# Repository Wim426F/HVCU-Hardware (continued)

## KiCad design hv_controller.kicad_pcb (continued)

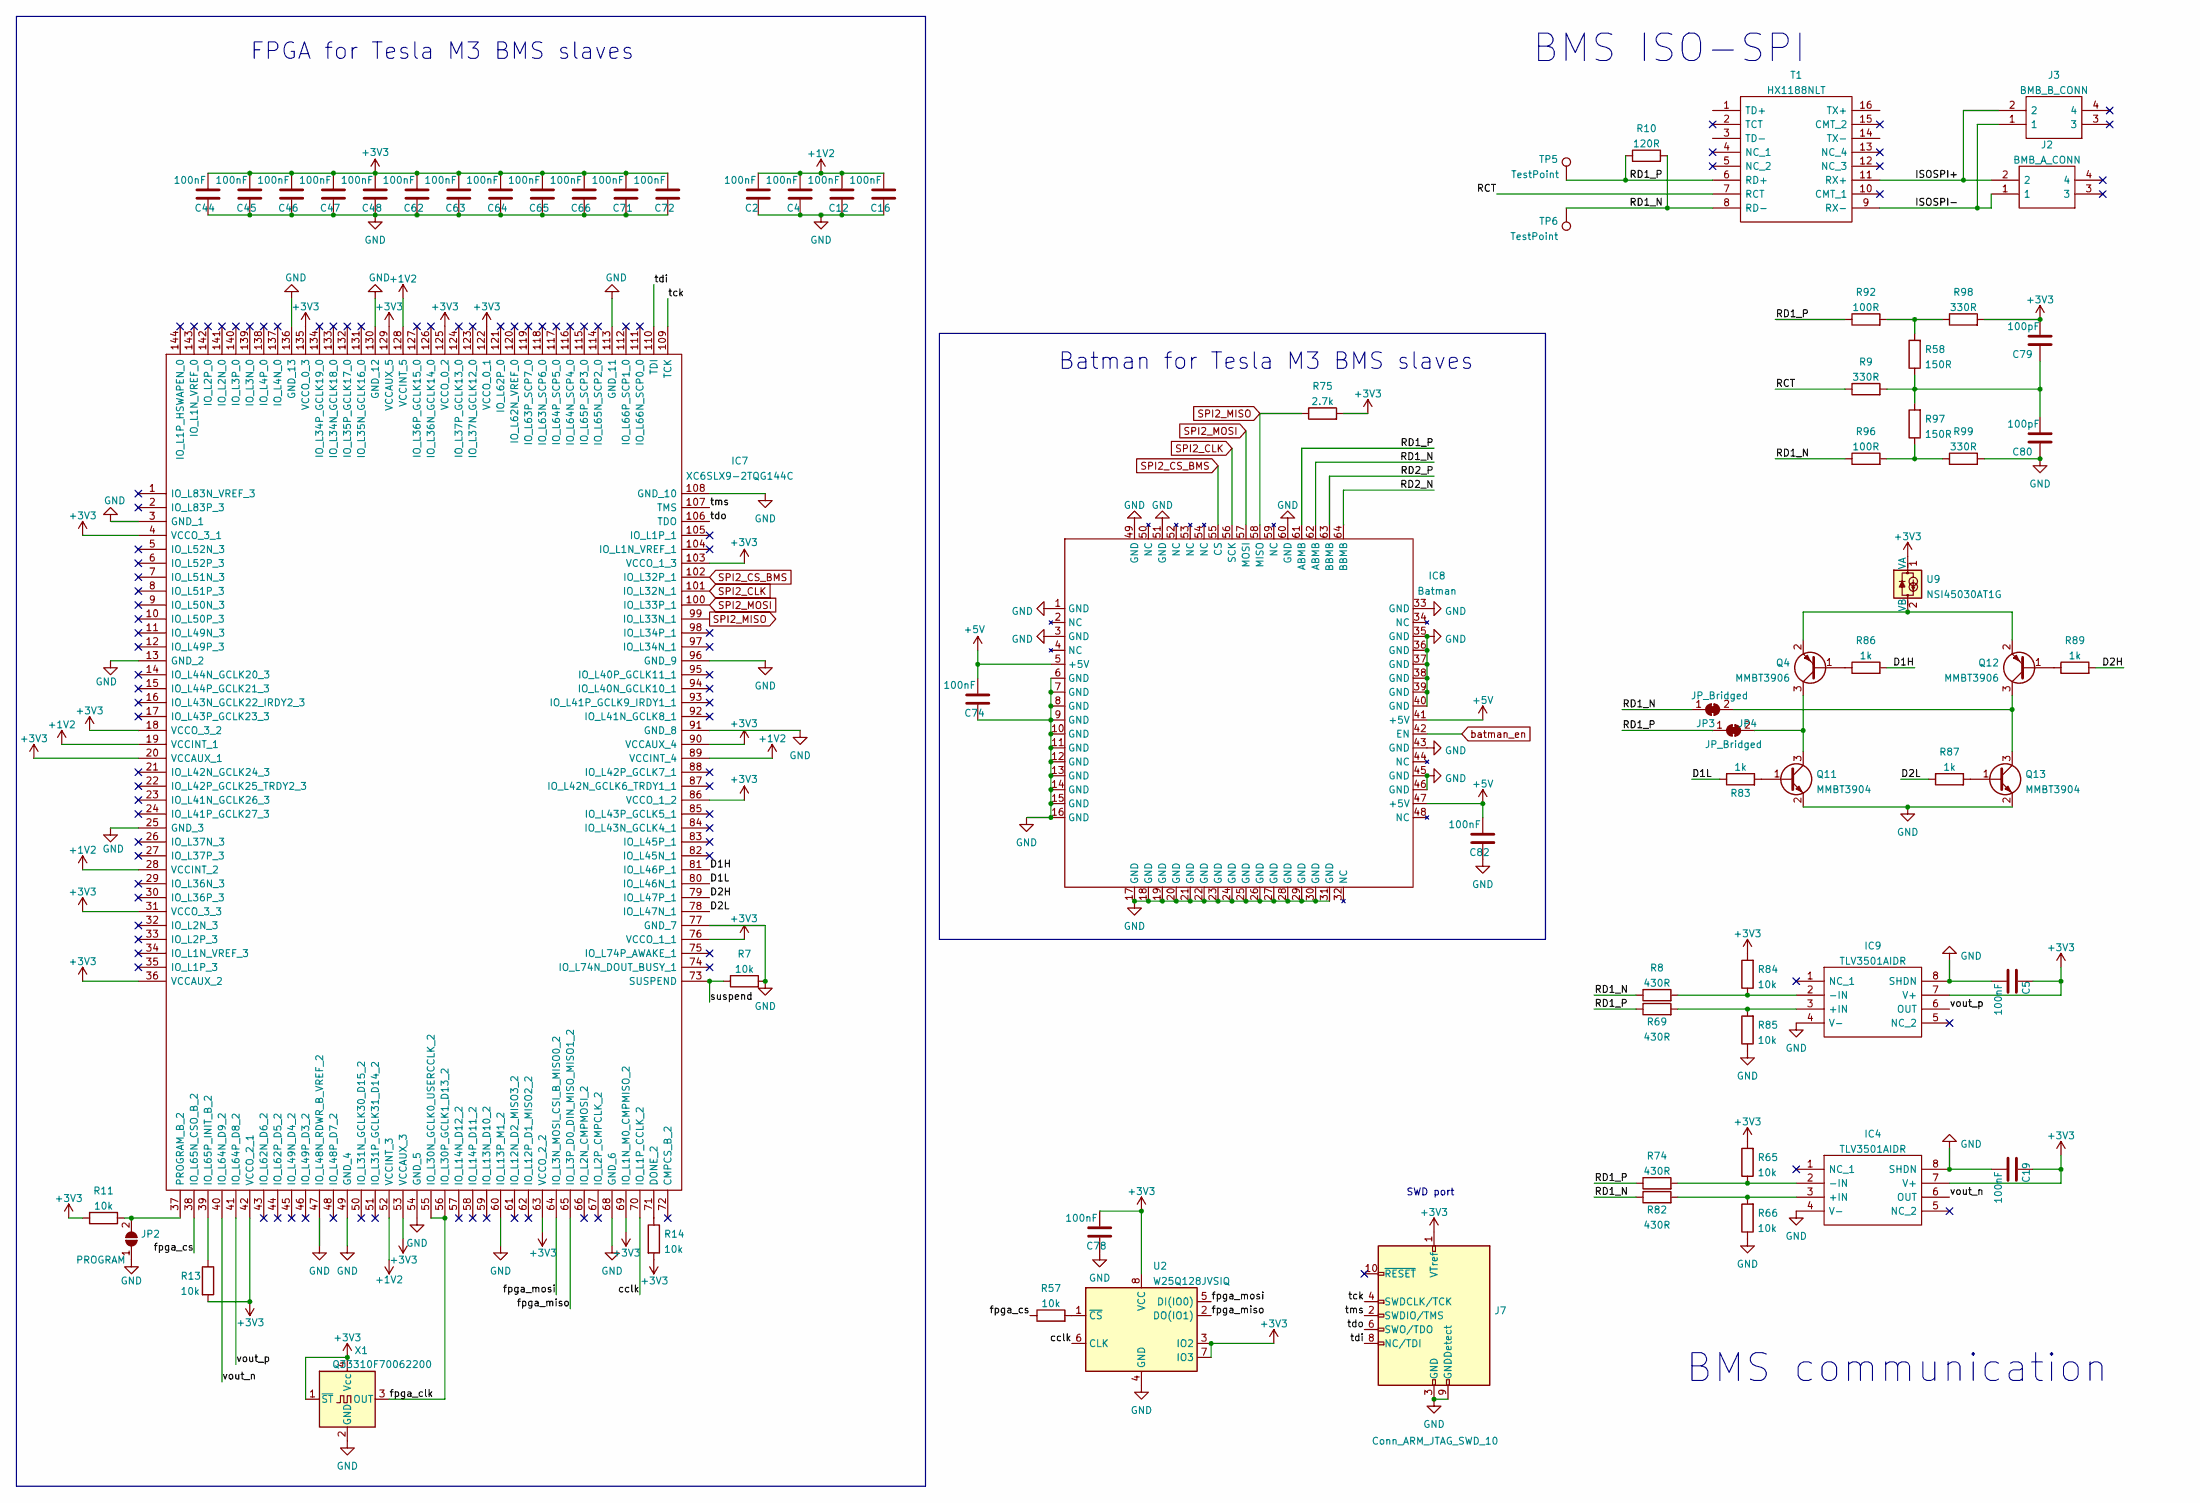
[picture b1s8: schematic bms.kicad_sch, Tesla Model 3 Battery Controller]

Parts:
C2, C4, C5, C12, C16, C19, C44, C45, C46, C47, C48, C62, C63, C64, C65, C66, C71, C72, C74, C78, C82: 100nF; C_0603_1608Metric; LCSC Part C14663
C79, C80: 100pF; C_0603_1608Metric; LCSC Part C14858
IC4, IC9: TLV3501AIDR; SOIC127P600X175-8N; Manufacturer_Part_Number TLV3501AIDR; Mouser Part Number 595-TLV3501AIDR
IC7: XC6SLX9-2TQG144C; QFP50P2200X2200X160-144N; Mouser Part Number 217-XC6SLX9-2TQG144C
IC8: Batman; LQFP-64_10x10mm_P0.5mm
J2: BMB_A_CONN; 0349128020; Manufacturer_Part_Number 34912-8020; Mouser Part Number 538-34912-8020
J3: BMB_B_CONN; 0349128020; Manufacturer_Part_Number 34912-8020; Mouser Part Number 538-34912-8020
J7: Conn_ARM_JTAG_SWD_10; PinHeader_2x05_P1.27mm_JTAG_SMD
JP2: PROGRAM; SolderJumper-2_P1.3mm_Open_RoundedPad1.0x1.5mm
JP3, JP4: JP_Bridged; SolderJumper-2_P1.3mm_Bridged_RoundedPad1.0x1.5mm
Q4, Q12: MMBT3906; SOT-23; LCSC Part C382282
Q11, Q13: MMBT3904; SOT-23; LCSC Part C20526
R7, R11, R13, R14, R57, R65, R66, R84, R85: 10k; R_0603_1608Metric; LCSC Part C25804
R8, R69, R74, R82: 430R; R_0603_1608Metric; LCSC Part C706174
R9, R98, R99: 330R; R_0603_1608Metric; LCSC Part C23138
R10: 120R; R_0603_1608Metric; LCSC Part C22787
R58, R97: 150R; R_0603_1608Metric; LCSC Part C22808
R75: 2.7k; R_0603_1608Metric; LCSC Part C13167
R83, R86, R87, R89: 1k; R_0603_1608Metric; LCSC Part C21190
R92, R96: 100R; R_0603_1608Metric; LCSC Part C22775
T1: HX1188NLT; Manufacturer_Part_Number HX1188NLT; Mouser Part Number 673-HX1188NLT
TP5, TP6: TestPoint
U2: W25Q128JVSIQ; SOIC-8_5.23x5.23mm_P1.27mm; LCSC Part C97521
U9: NSI45030AT1G; D_SOD-123; LCSC Part C150066
X1: Q33310F70062200; Oscillator_SMD_SeikoEpson_SG8002CE-4Pin_3.2x2.5mm; LCSC Part C46327

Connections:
+1V2: C2.1, C4.1, C12.1, C16.1, IC7.19 (VCCINT_1), IC7.28 (VCCINT_2), IC7.52 (VCCINT_3), IC7.89 (VCCINT_4), IC7.128 (VCCINT_5); also elsewhere on the board
+5V: C74.1, C82.1, IC8.5 (+5V), IC8.41 (+5V), IC8.47 (+5V); also elsewhere on the board
/BMS communication/D1H: IC7.81 (IO_L46P_1), R86.2
/BMS communication/D1L: IC7.80 (IO_L46N_1), R83.1
/BMS communication/D2H: IC7.79 (IO_L47P_1), R89.2
/BMS communication/D2L: IC7.78 (IO_L47N_1), R87.1
/BMS communication/ISOSPI+: J2.2, J3.2, T1.11 (RX+)
/BMS communication/ISOSPI-: J2.1, J3.1, T1.9 (RX-)
/BMS communication/RCT: R9.1, T1.7 (RCT)
/BMS communication/RD1_N: IC8.62 (ABMB), JP3.1 (A), R8.1, R10.2, R82.1, R96.1, T1.8 (RD-), TP6.1
/BMS communication/RD1_P: IC8.61 (ABMB), JP4.1 (A), R10.1, R69.1, R74.1, R92.1, T1.6 (RD+), TP5.1
/BMS communication/RD2_N: IC8.64 (BBMB)
/BMS communication/RD2_P: IC8.63 (BBMB)
/BMS communication/cclk: IC7.70 (IO_L1P_CCLK_2), U2.6 (CLK)
/BMS communication/fpga_clk: IC7.55 (IO_L30N_GCLK0_USERCCLK_2), IC7.56 (IO_L30P_GCLK1_D13_2), X1.3 (OUT)
/BMS communication/fpga_cs: IC7.38 (IO_L65N_CSO_B_2), R57.1
/BMS communication/fpga_miso: IC7.65 (IO_L3P_D0_DIN_MISO_MISO1_2), U2.2 (DO(IO1))
/BMS communication/fpga_mosi: IC7.64 (IO_L3N_MOSI_CSI_B_MISO0_2), U2.5 (DI(IO0))
/BMS communication/suspend: IC7.73 (SUSPEND), R7.1
/BMS communication/tck: IC7.109 (TCK), J7.4 (SWDCLK/TCK)
/BMS communication/tdi: IC7.110 (TDI), J7.8 (NC/TDI)
/BMS communication/tdo: IC7.106 (TDO), J7.6 (SWO/TDO)
/BMS communication/tms: IC7.107 (TMS), J7.2 (SWDIO/TMS)
/BMS communication/vout_n: IC4.6 (OUT), IC7.40 (IO_L64N_D9_2)
/BMS communication/vout_p: IC7.41 (IO_L64P_D8_2), IC9.6 (OUT)
GND: C2.2, C4.2, C5.1, C12.2, C16.2, C19.1, C44.2, C45.2, C46.2, C47.2, C48.2, C62.2, C63.2, C64.2, C65.2, C66.2, C71.2, C72.2, C74.2, C78.2, C80.1, C82.2, IC4.4 (V-), IC4.8 (SHDN), IC7.3 (GND_1), IC7.13 (GND_2), IC7.25 (GND_3), IC7.47 (IO_L48N_RDWR_B_VREF_2), IC7.49 (GND_4), IC7.54 (GND_5), IC7.60 (IO_L13P_M1_2), IC7.68 (GND_6), IC7.77 (GND_7), IC7.91 (GND_8), IC7.96 (GND_9), IC7.108 (GND_10), IC7.113 (GND_11), IC7.130 (GND_12), IC7.136 (GND_13), IC8.1 (GND), IC8.3 (GND), IC8.6 (GND), IC8.7 (GND), IC8.8 (GND), IC8.9 (GND), IC8.10 (GND), IC8.11 (GND), IC8.12 (GND), IC8.13 (GND), IC8.14 (GND), IC8.15 (GND), IC8.16 (GND), IC8.17 (GND), IC8.18 (GND), IC8.19 (GND), IC8.20 (GND), IC8.21 (GND), IC8.22 (GND), IC8.23 (GND), IC8.24 (GND), IC8.25 (GND), IC8.26 (GND), IC8.27 (GND), IC8.28 (GND), IC8.29 (GND), IC8.30 (GND), IC8.31 (GND), IC8.33 (GND), IC8.35 (GND), IC8.36 (GND), IC8.37 (GND), IC8.38 (GND), IC8.39 (GND), IC8.40 (GND), IC8.43 (GND), IC8.45 (GND), IC8.46 (GND), IC8.49 (GND), IC8.51 (GND), IC8.60 (GND), IC9.4 (V-), IC9.8 (SHDN), J7.3 (GND), J7.5 (GND), J7.9 (GNDDetect), JP2.1 (A), Q11.2 (E), Q13.2 (E), R7.2, R66.1, R85.1, R99.2, U2.4 (GND), X1.2 (GND); also elsewhere on the board
unnamed: C79.1, C80.2, R9.2, R58.1, R97.2
unnamed: IC4.3 (+IN), R66.2, R82.2
unnamed: IC4.2 (-IN), R65.1, R74.2
unnamed: IC7.71 (DONE_2), R14.1
unnamed: IC7.39 (IO_L65P_INIT_B_2), R13.1
unnamed: IC7.37 (PROGRAM_B_2), JP2.2 (B), R11.1
unnamed: IC9.3 (+IN), R69.2, R85.2
unnamed: IC9.2 (-IN), R8.2, R84.1
unnamed: JP3.2 (B), Q12.3 (C), Q13.3 (C)
unnamed: JP4.2 (B), Q4.3 (C), Q11.3 (C)
unnamed: Q4.1 (B), R86.1
unnamed: Q11.1 (B), R83.2
unnamed: Q12.1 (B), R89.1
unnamed: Q4.2 (E), Q12.2 (E), U9.2 (VB)
unnamed: Q13.1 (B), R87.2
unnamed: R58.2, R92.2, R98.1
unnamed: R96.2, R97.1, R99.1
unnamed: R57.2, U2.1 (~CS)
SPI2_CLK: IC7.101 (IO_L32N_1), IC8.56 (SCK); also elsewhere on the board
SPI2_CS_BMS: IC7.102 (IO_L32P_1), IC8.55 (CS); also elsewhere on the board
SPI2_MISO: IC7.99 (IO_L33N_1), IC8.58 (MISO), R75.1; also elsewhere on the board
SPI2_MOSI: IC7.100 (IO_L33P_1), IC8.57 (MOSI); also elsewhere on the board
batman_en: IC8.42 (EN); also elsewhere on the board

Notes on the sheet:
BMS communication
Batman for Tesla M3 BMS slaves
BMS ISO-SPI
SWD port
FPGA for Tesla M3 BMS slaves

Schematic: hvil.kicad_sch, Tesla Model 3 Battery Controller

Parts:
D10, D12, D13, D14, D16: ZMM3V3-M; D_MiniMELF; LCSC Part C8056
R6, R70, R71, R72, R73: 10k; R_0603_1608Metric; LCSC Part C25804

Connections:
/HVIL safety/HVIL_CONN_OUT: R70.1; also elsewhere on the board
/HVIL safety/HVIL_IN: R6.2; also elsewhere on the board
/HVIL safety/HVIL_SC_CONN_OUT: R72.1; also elsewhere on the board
/HVIL safety/SCNEG_LATCH_OUT: R71.1; also elsewhere on the board
/HVIL safety/SCPOS_LATCH_OUT: R73.1; also elsewhere on the board
GND: D10.2 (A), D12.2 (A), D13.2 (A), D14.2 (A), D16.2 (A); also elsewhere on the board
hvil_conn_ok: D12.1 (K), R70.2; also elsewhere on the board
hvil_sc_conn_ok: D14.1 (K), R72.2; also elsewhere on the board
latch_scneg_ok: D13.1 (K), R71.2; also elsewhere on the board
latch_scpos_ok: D16.1 (K), R73.2; also elsewhere on the board

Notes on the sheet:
HVIL and continuity check

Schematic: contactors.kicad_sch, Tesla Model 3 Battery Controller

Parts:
C14, C15, C21, C24: 10nF; C_0603_1608Metric; LCSC Part C57112
D4, D5, D6, D7: SVM1045V; TO-277B; LCSC Part C268715
IC1, IC3: UCC27324DR; SOP-8_3.9x4.9mm_P1.27mm; Manufacturer_Part_Number UCC27324DR; LCSC Part C46427
Q6, Q7, Q8, Q9: SIR802DP-T1-GE3-VB; SIRA90DPT1GE3; Manufacturer_Part_Number SIR802DP-T1-GE3-VB; LCSC Part C558278

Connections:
+12V: D4.3 (K), D5.3 (K), D6.3 (K), D7.3 (K), IC1.6 (VDD), IC3.6 (VDD); also elsewhere on the board
/Contactors/CCS_NEG: C14.1, D5.1 (A), D5.2 (A), Q8.5 (D_1), Q8.6 (D_2), Q8.7 (D_3), Q8.8 (D_4), Q8.9 (D_5); also elsewhere on the board
/Contactors/CCS_POS: C15.1, D4.1 (A), D4.2 (A), Q9.5 (D_1), Q9.6 (D_2), Q9.7 (D_3), Q9.8 (D_4), Q9.9 (D_5); also elsewhere on the board
/Contactors/MCON_NEG: C21.1, D6.1 (A), D6.2 (A), Q6.5 (D_1), Q6.6 (D_2), Q6.7 (D_3), Q6.8 (D_4), Q6.9 (D_5); also elsewhere on the board
/Contactors/MCON_POS: C24.1, D7.1 (A), D7.2 (A), Q7.5 (D_1), Q7.6 (D_2), Q7.7 (D_3), Q7.8 (D_4), Q7.9 (D_5); also elsewhere on the board
CCS_NEG_EN: IC1.5 (OUT_B), Q8.4 (G)
CCS_POS_EN: IC1.7 (OUT_A), Q9.4 (G)
GND: C14.2, C15.2, C21.2, C24.2, IC1.3 (GND), IC3.3 (GND), Q6.1 (S_1), Q6.2 (S_2), Q6.3 (S_3), Q7.1 (S_1), Q7.2 (S_2), Q7.3 (S_3), Q8.1 (S_1), Q8.2 (S_2), Q8.3 (S_3), Q9.1 (S_1), Q9.2 (S_2), Q9.3 (S_3); also elsewhere on the board
unnamed: IC3.7 (OUT_A), Q6.4 (G)
unnamed: IC3.5 (OUT_B), Q7.4 (G)
gate_ccs_n: IC1.4 (IN_B); also elsewhere on the board
gate_ccs_p: IC1.2 (IN_A); also elsewhere on the board
gate_mcon_n: IC3.4 (IN_B); also elsewhere on the board
gate_mcon_p: IC3.2 (IN_A); also elsewhere on the board

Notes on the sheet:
ss54 400mV@1A 25C old 30BQ015 280mV@1A 25C X SVM1045V 290mV@1A 25C 370mV@5A 25C ST54BF 270mV@1A 25C 370mV@5A 25C best: SVM1045V
Main battery contactors
CCS contactors
Contactors
pulldown must be done in microcontroller

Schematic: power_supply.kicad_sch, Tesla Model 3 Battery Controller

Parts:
C8, C30, C32, C84: 10uF; C_0603_1608Metric; LCSC Part C19702
C28, C29: 4.7uF; C_0603_1608Metric; LCSC Part C19666
C35, C92: 3.3nF; C_0603_1608Metric; LCSC Part C1613
C38, C41, C42, C55: 22uF; C_0603_1608Metric; LCSC Part C59461
C39: 1uF; C_0603_1608Metric; LCSC Part C15849
C40, C91: 10nF; C_0603_1608Metric; LCSC Part C57112
C43, C90: 47nF; C_0603_1608Metric; LCSC Part C1622
C73, C81: 4.7uF; C_0805_2012Metric_Pad1.18x1.45mm_HandSolder; LCSC Part C1779
C75, C83: 220uf_25V; CP_Elec_6.3x7.7; Part nr. GYA1E221MCQ1GS; LCSC Part C371974
C86: 680pF 630V; C_1206_3216Metric_Pad1.33x1.80mm_HandSolder; Part nr CS85-B2GA681KANKA; LCSC Part C106005
C87: 22uf_450V; C_Radial_D12.5mm_H20.0mm_P5.00mm; Mouser UUG2G220MNQ6MS
C93: 10uF; C_0805_2012Metric_Pad1.18x1.45mm_HandSolder; LCSC Part C440198
F1: A600-150; Fuse_RL600-150_L14mm_W5.1mm; LCSC Part C135449
IC2: TPS65261RHBR; HVQFN-32-1EP_5x5mm_P0.5mm_EP3.1x3.1mm; Manufacturer_Part_Number TPS65261RHBR; Mouser Part Number 595-TPS65261RHBR
L1: 2.2uH; L_0805_2012Metric_Pad1.15x1.40mm_HandSolder; LCSC Part C136243
L2, L3: 4.7uH; L_Vishay_IFSC-1515AH_4x4x1.8mm; LCSC Part C602031
L4, L5: 6.8uH; L_0805_2012Metric_Pad1.15x1.40mm_HandSolder; LCSC Part C139247
Q15: AGM30P100A; PQFN-8-EP_6x5mm_P1.27mm_Generic; LCSC Part C5297493
R17, R107: 5.1k; R_0603_1608Metric; LCSC Part C23186
R18, R105: 1k; R_0603_1608Metric; LCSC Part C21190
R94: 15k; R_0603_1608Metric; LCSC Part C22809
R95: 68k; R_0603_1608Metric; LCSC Part C23231
R100, R101: 10kΩ; R_0402_1005Metric_Pad0.72x0.64mm_HandSolder; LCSC Part C328417
R104, R111: 20k; R_0603_1608Metric; LCSC Part C4184
R106: 30k; R_0603_1608Metric; LCSC Part C22984
R108, R110: 73.2k; R_0603_1608Metric; LCSC Part C321992
R109: 10k; R_0603_1608Metric; LCSC Part C25804
T2: EPM1510SJA; Converter_DCDC_EPM1205SJ; Manufacturer_Part_Number EPM1510SJA; Mouser Part Number 838-EPM1205SJ
T3: IES0105S12; SMDIP-8_W9.53mm
T5: IES0105S05; SMDIP-8_W9.53mm
U3: LD1117S12TR_SOT223; SOT-223-3_TabPin2; LCSC Part C155612
U17: HT7550-1; SOT-89-3; LCSC Part C16106

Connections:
12V_VEH: Q15.5 (D); also elsewhere on the board
+1V2: U3.2 (VO); also elsewhere on the board
+5V: C29.1, C42.1, C55.1, C73.1, L3.2, L4.1, L5.1, R108.1; also elsewhere on the board
+5VA: C30.2, T5.5 (+Vout); also elsewhere on the board
+5VD: C84.1, U17.2 (VO); also elsewhere on the board
+12V: IC2.12 (PVIN2), IC2.28 (PVIN1), IC2.29 (VIN), Q15.1 (S), Q15.2 (S), Q15.3 (S), R17.2, R106.2; also elsewhere on the board
+12VA: C8.1, C75.1, C93.2, L1.2, T3.5 (+Vout), U17.3 (VI); also elsewhere on the board
/HVBATT_NEG: C86.1, C87.2, T2.10 (-DC_IN); also elsewhere on the board
/HVBATT_POS: F1.2; also elsewhere on the board
/Power supply/+vin: C28.1, C81.1, L4.2, L5.2, T3.2 (+Vin), T5.2 (+Vin)
/Power supply/bst1: C90.1, IC2.25 (BST1)
/Power supply/bst2: C43.2, IC2.9 (BST2)
/Power supply/comp1: IC2.23 (COMP1), R111.2
/Power supply/comp2: IC2.7 (COMP2), R104.2
/Power supply/en3: IC2.1 (EN3), R105.1
/Power supply/fb1: IC2.22 (FB1), R108.2, R109.2
/Power supply/fb2: IC2.6 (FB2), R94.1, R95.2
/Power supply/lx1: C90.2, IC2.26 (LX1), L3.1
/Power supply/lx2: C43.1, IC2.10 (LX2), L2.2
/Power supply/rosc: IC2.20 (ROSC), R110.1
/Power supply/ss1: C91.1, IC2.24 (SS1)
/Power supply/ss2: C40.1, IC2.8 (SS2)
/Power supply/v7v: C39.2, IC2.5 (V7V)
/Power supply/vdiv: IC2.30 (VDIV), R106.1, R107.1
GND: C28.2, C29.2, C32.1, C35.2, C38.2, C39.1, C40.2, C41.2, C42.2, C55.2, C73.2, C81.2, C91.2, C92.2, IC2.4 (MODE), IC2.11 (PGND2), IC2.14 (PGND3), IC2.21 (AGND), IC2.27 (PGND1), IC2.33 (EP), Q15.4 (G), R18.1, R94.2, R101.1, R105.2, R107.2, R109.1, R110.2, T3.1 (-Vin), T5.1 (-Vin), U3.1 (GND); also elsewhere on the board
GND1: C30.1, T5.4 (-Vout); also elsewhere on the board
unnamed: C35.1, R104.1
unnamed: C92.1, R111.1
unnamed: C87.1, F1.1, T2.12 (+DC_IN)
unnamed: C83.1, L1.1, T2.5 (+DC_OUT)
VREF_1.8V: C32.2, R100.1, R101.2; also elsewhere on the board
uaux: R17.1, R18.2

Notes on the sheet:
Isolated Power supply for shunt & pyro circuit
Power supply for 3.3V & 5V
minimum current draw must be 8mA
3.3V to 1.2V for fpga
12V measurement
Reference Voltage for isolation monitoring
Power supply
Isolated Power supply for voltage measurement
Reverse voltage protection
12V to 5V for pyrofuse control circuit

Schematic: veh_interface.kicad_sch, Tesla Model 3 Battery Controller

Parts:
C20, C22, C23, C36, C37, C50: 100nF; C_0603_1608Metric; LCSC Part C14663
D15: SZNUP2105LT1G; SOT-23; LCSC Part C233494
IC5: SN65C3232EDR; SOIC127P600X175-16N; Manufacturer_Part_Number SN65C3232EDR; Mouser Part Number 595-SN65C3232EDR
J1: VEH_INTERFACE; Molex_Mini-Fit_Jr_5569-08A2_2x04_P4.20mm_Horizontal
J12: CAN_DEBUG; TestPoint_2Pads_Pitch2.54mm_Drill0.8mm
JP1: SolderJumper_2_Open; SolderJumper-2_P1.3mm_Open_RoundedPad1.0x1.5mm
L6: L_Coupled_1423; PE1812ACC220STS; Manufacturer_Part_Number PE-1812ACC220STS; Mouser Part Number 673-PE-1812ACC220STS
Q5: MMBT5401; SOT-23; LCSC Part C8326
Q14: MMBT5551; SOT-23; LCSC Part C2145
R15, R19, R77: 10k; R_0603_1608Metric; LCSC Part C25804
R16: 2.7k; R_0603_1608Metric; LCSC Part C13167
R80: 5.1k; R_0603_1608Metric; LCSC Part C23186
R93: 120R; R_0603_1608Metric; LCSC Part C22787
U11: TJA1050T/CM,118; SOIC-8_3.9x4.9mm_P1.27mm; LCSC Part C6952
U13: ESP32-C3 SuperMini; ESP32-C3-14P-SMD-2.54-21X17.8MM

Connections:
12V_VEH: J1.1; also elsewhere on the board
+12V: Q5.2 (E), R77.1; also elsewhere on the board
/Vehicle interface/GPIO_1: J1.3, Q5.3 (C), R15.2
/Vehicle interface/RS232_RX: IC5.13 (RIN1), J1.6
/Vehicle interface/RS232_TX: IC5.14 (DOUT1), J1.5
/Vehicle interface/c1+: C20.2, IC5.1 (C1+)
/Vehicle interface/c1-: C20.1, IC5.3 (C1-)
/Vehicle interface/c2+: C22.2, IC5.4 (C2+)
/Vehicle interface/c2-: C22.1, IC5.5 (C2-)
/Vehicle interface/v+: C36.1, IC5.2 (V+)
/Vehicle interface/v-: C23.2, IC5.6 (V-)
GND: C23.1, C36.2, C37.1, C50.1, D15.3 (A), IC5.15 (GND), J1.2, Q14.2 (E), R16.1, U11.2 (GND), U11.8 (STB), U13.15 (GND); also elsewhere on the board
unnamed: JP1.2 (B), R93.2
unnamed: Q5.1 (B), R77.2, R80.2
unnamed: Q14.1 (B), R19.2
unnamed: Q14.3 (C), R80.1
PT_CAN_H: D15.1 (K), J1.7, J12.1, L6.4
PT_CAN_L: D15.2 (K), J1.8, J12.2, L6.3
ptcan1_rx: U11.4 (RXD); also elsewhere on the board
ptcan1_tx: U11.1 (TXD); also elsewhere on the board
ptcan_h: JP1.1 (A), L6.2, U11.6 (CANL)
ptcan_l: L6.1, R93.1, U11.7 (CANH)
usart1_rx1: IC5.12 (ROUT1); also elsewhere on the board
usart1_tx1: IC5.11 (DIN1); also elsewhere on the board
veh_gpi: R15.1, R16.2; also elsewhere on the board
veh_gpo: R19.1; also elsewhere on the board
wifi_rx: U13.8 (GPIO21_TX); also elsewhere on the board
wifi_tx: U13.7 (GPIO20_RX); also elsewhere on the board

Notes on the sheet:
TTL <-> RS232
Vehicle interface
12V GPIO

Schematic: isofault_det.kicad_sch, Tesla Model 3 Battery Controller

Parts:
C31: 100nF; C_0603_1608Metric; LCSC Part C14663
R20, R23, R26, R29, R32, R35: 402k; R_0805_2012Metric_Pad1.20x1.40mm_HandSolder; LCSC Part C706240
R38, R39, R44, R45, R59, R60: 10k; R_0603_1608Metric; LCSC Part C25804
R50, R51: 5.1k; R_0603_1608Metric; LCSC Part C23186
TP1: ISO_POS; TestPoint_THTPad_1.5x1.5mm_Drill0.7mm
TP2: ISO_NEG; TestPoint_THTPad_1.5x1.5mm_Drill0.7mm
U7, U10: C238S; SO-4_4.4x4.3mm_P2.54mm
U19: LM358; SOIC-8_3.9x4.9mm_P1.27mm; LCSC Part C7950

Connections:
/HVBATT_NEG: R23.1; also elsewhere on the board
/HVBATT_POS: R20.1; also elsewhere on the board
GND: C31.1, R59.1, R60.1, U7.2, U10.2, U19.4 (V-); also elsewhere on the board
ISO_BATT_NEG: R51.2, R60.2, TP2.1, U19.7; also elsewhere on the board
ISO_BATT_POS: R50.2, R59.2, TP1.1, U19.1; also elsewhere on the board
unnamed: R20.2, R26.1
unnamed: R23.2, R29.1
unnamed: R26.2, R35.1
unnamed: R29.2, R32.1
unnamed: R32.2, U10.4
unnamed: R35.2, U7.4
unnamed: R38.1, U7.3
unnamed: R39.1, U10.3
unnamed: R44.1, U7.1
unnamed: R45.1, U10.1
unnamed: R38.2, R50.1, U19.2 (-)
unnamed: R39.2, R51.1, U19.6 (-)
SW_BNEG: R45.2; also elsewhere on the board
SW_BPOS: R44.2; also elsewhere on the board
VREF_1.8V: U19.3 (+), U19.5 (+); also elsewhere on the board

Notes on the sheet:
Isolation Resistance measurement

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
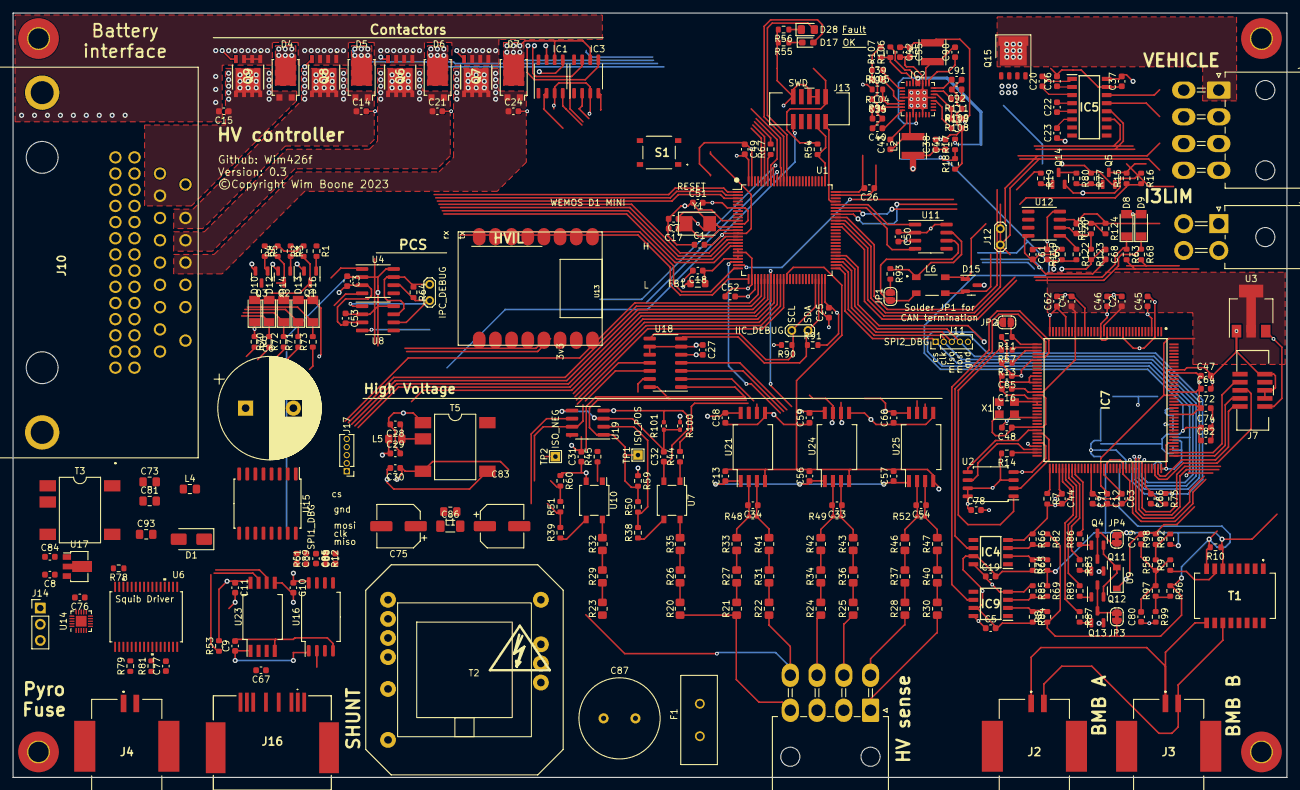
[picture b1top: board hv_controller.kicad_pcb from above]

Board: 4 copper layers, 200.0 x 120.0 mm, 300 parts (1 on the bottom side), 233 nets.

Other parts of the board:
C10: 1nF; C_0603_1608Metric
